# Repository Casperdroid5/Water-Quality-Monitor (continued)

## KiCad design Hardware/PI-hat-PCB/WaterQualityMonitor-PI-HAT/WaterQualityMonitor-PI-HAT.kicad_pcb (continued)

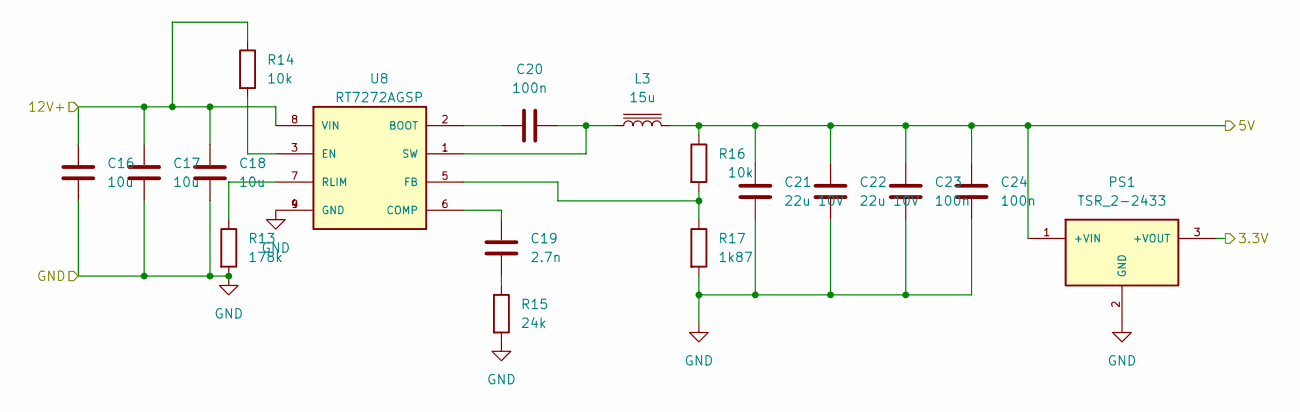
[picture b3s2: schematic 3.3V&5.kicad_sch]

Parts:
C16, C17, C18: 10u; C_1206_3216Metric_Pad1.33x1.80mm_HandSolder
C19: 2.7n; C_1206_3216Metric_Pad1.33x1.80mm_HandSolder
C20, C23, C24: 100n; C_1206_3216Metric_Pad1.33x1.80mm_HandSolder
C21, C22: 22u 10V; C_1206_3216Metric_Pad1.33x1.80mm_HandSolder
L3: 15u; L_1206_3216Metric_Pad1.22x1.90mm_HandSolder
PS1: TSR_2-2433; Converter_DCDC_TRACO_TSR-1_THT; PARTREV May 14, 2020
R13: 178k; R_1206_3216Metric_Pad1.30x1.75mm_HandSolder
R14, R16: 10k; R_1206_3216Metric_Pad1.30x1.75mm_HandSolder
R15: 24k; R_1206_3216Metric_Pad1.30x1.75mm_HandSolder
R17: 1k87; R_1206_3216Metric_Pad1.30x1.75mm_HandSolder
U8: RT7272AGSP; SOIC127P599X175-9N; PARTREV June 2015

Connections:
3.3V: PS1.3 (+VOUT); also elsewhere on the board
5V: C21.2, C22.2, C23.2, C24.1, L3.2, PS1.1 (+VIN), R16.1; also elsewhere on the board
12V+: C16.1, C17.1, C18.1, R14.1, U8.8 (VIN); also elsewhere on the board
GND: C16.2, C17.2, C18.2, C21.1, C22.1, C23.1, C24.2, PS1.2 (GND), R13.2, R15.2, R17.2, U8.4 (GND), U8.9 (GND); also elsewhere on the board
unnamed: C19.1, R15.1
unnamed: C19.2, U8.6 (COMP)
unnamed: C20.1, U8.2 (BOOT)
unnamed: C20.2, L3.1, U8.1 (SW)
unnamed: R13.1, U8.7 (RLIM)
unnamed: R14.2, U8.3 (EN)
unnamed: R16.2, R17.1, U8.5 (FB)

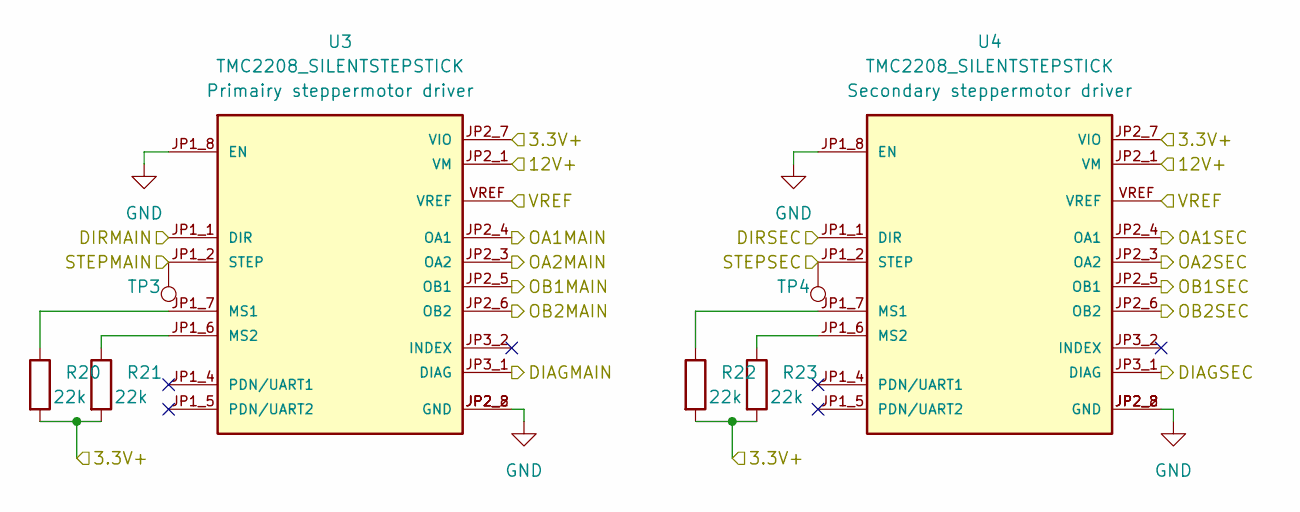
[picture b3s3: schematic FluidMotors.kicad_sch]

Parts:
R20, R21, R22, R23: 22k; R_1206_3216Metric_Pad1.30x1.75mm_HandSolder
TP3, TP4: TestPoint; TestPoint_Keystone_5019_Minature
U3, U4: TMC2208_SILENTSTEPSTICK

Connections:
3.3V: R20.2, R21.2, R22.2, R23.2, U3.JP2_7 (VIO), U3.VREF, U4.JP2_7 (VIO), U4.VREF; also elsewhere on the board
12V+: U3.JP2_1 (VM), U4.JP2_1 (VM); also elsewhere on the board
/FluidMotors/DIAGMAIN: U3.JP3_1 (DIAG)
/FluidMotors/DIAGSEC: U4.JP3_1 (DIAG)
/FluidMotors/OA1MAIN: U3.JP2_4 (OA1); also elsewhere on the board
/FluidMotors/OA1SEC: U4.JP2_4 (OA1); also elsewhere on the board
/FluidMotors/OA2MAIN: U3.JP2_3 (OA2); also elsewhere on the board
/FluidMotors/OA2SEC: U4.JP2_3 (OA2); also elsewhere on the board
/FluidMotors/OB1MAIN: U3.JP2_5 (OB1); also elsewhere on the board
/FluidMotors/OB1SEC: U4.JP2_5 (OB1); also elsewhere on the board
/FluidMotors/OB2MAIN: U3.JP2_6 (OB2); also elsewhere on the board
/FluidMotors/OB2SEC: U4.JP2_6 (OB2); also elsewhere on the board
DIRMAIN: U3.JP1_1 (DIR); also elsewhere on the board
DIRSEC: U4.JP1_1 (DIR); also elsewhere on the board
GND: U3.JP1_8 (EN), U3.JP2_2 (GND), U3.JP2_8 (GND), U4.JP1_8 (EN), U4.JP2_2 (GND), U4.JP2_8 (GND); also elsewhere on the board
unnamed: R21.1, U3.JP1_6 (MS2)
unnamed: R20.1, U3.JP1_7 (MS1)
unnamed: R23.1, U4.JP1_6 (MS2)
unnamed: R22.1, U4.JP1_7 (MS1)
STEPMAIN: TP3.1, U3.JP1_2 (STEP); also elsewhere on the board
STEPSEC: TP4.1, U4.JP1_2 (STEP); also elsewhere on the board

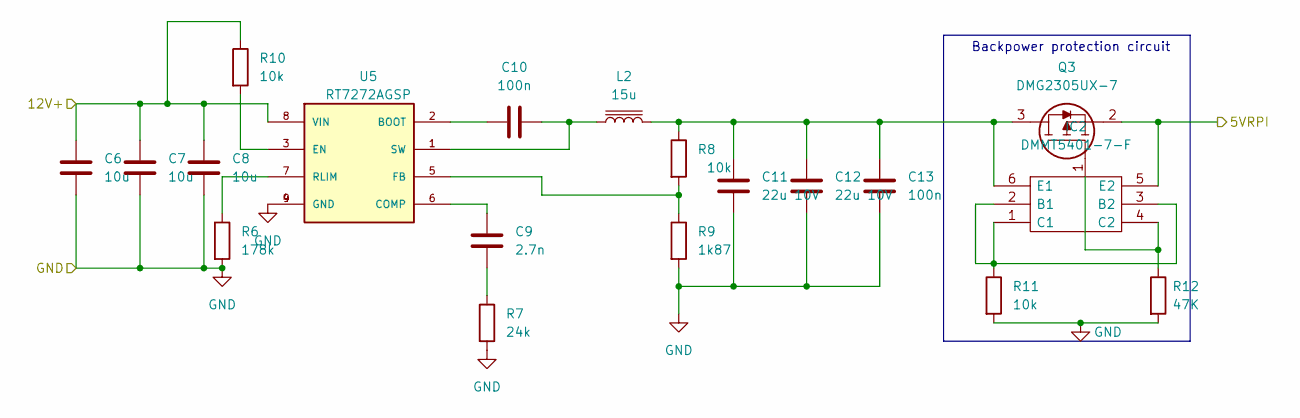
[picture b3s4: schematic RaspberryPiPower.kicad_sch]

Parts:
C6, C7, C8: 10u; C_1206_3216Metric_Pad1.33x1.80mm_HandSolder
C9: 2.7n; C_1206_3216Metric_Pad1.33x1.80mm_HandSolder
C10, C13: 100n; C_1206_3216Metric_Pad1.33x1.80mm_HandSolder
C11, C12: 22u 10V; C_1206_3216Metric_Pad1.33x1.80mm_HandSolder
IC2: DMMT5401-7-F; SOT95P285X140-6N; Mouser Part Number 621-DMMT5401-7-F
L2: 15u; L_1206_3216Metric_Pad1.22x1.90mm_HandSolder
Q3: DMG2305UX-7; SOT91P240X110-3N_DMG2305UX-7; Mouser Part Number 621-DMG2305UX-7
R6: 178k; R_1206_3216Metric_Pad1.30x1.75mm_HandSolder
R7: 24k; R_1206_3216Metric_Pad1.30x1.75mm_HandSolder
R8, R10, R11: 10k; R_1206_3216Metric_Pad1.30x1.75mm_HandSolder
R9: 1k87; R_1206_3216Metric_Pad1.30x1.75mm_HandSolder
R12: 47K; R_1206_3216Metric_Pad1.30x1.75mm_HandSolder
U5: RT7272AGSP; SOIC127P599X175-9N; PARTREV June 2015

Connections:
5VRPI: IC2.5 (E2), Q3.2; also elsewhere on the board
12V+: C6.1, C7.1, C8.1, R10.1, U5.8 (VIN); also elsewhere on the board
GND: C6.2, C7.2, C8.2, C11.1, C12.1, C13.1, R6.2, R7.2, R9.2, R11.2, R12.2, U5.4 (GND), U5.9 (GND); also elsewhere on the board
unnamed: C9.1, R7.1
unnamed: C9.2, U5.6 (COMP)
unnamed: C10.1, U5.2 (BOOT)
unnamed: C10.2, L2.1, U5.1 (SW)
unnamed: C11.2, C12.2, C13.2, IC2.6 (E1), L2.2, Q3.3, R8.1
unnamed: IC2.1 (C1), IC2.2 (B1), IC2.3 (B2), R11.1
unnamed: IC2.4 (C2), Q3.1, R12.1
unnamed: R6.1, U5.7 (RLIM)
unnamed: R8.2, R9.1, U5.5 (FB)
unnamed: R10.2, U5.3 (EN)

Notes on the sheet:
Backpower protection circuit

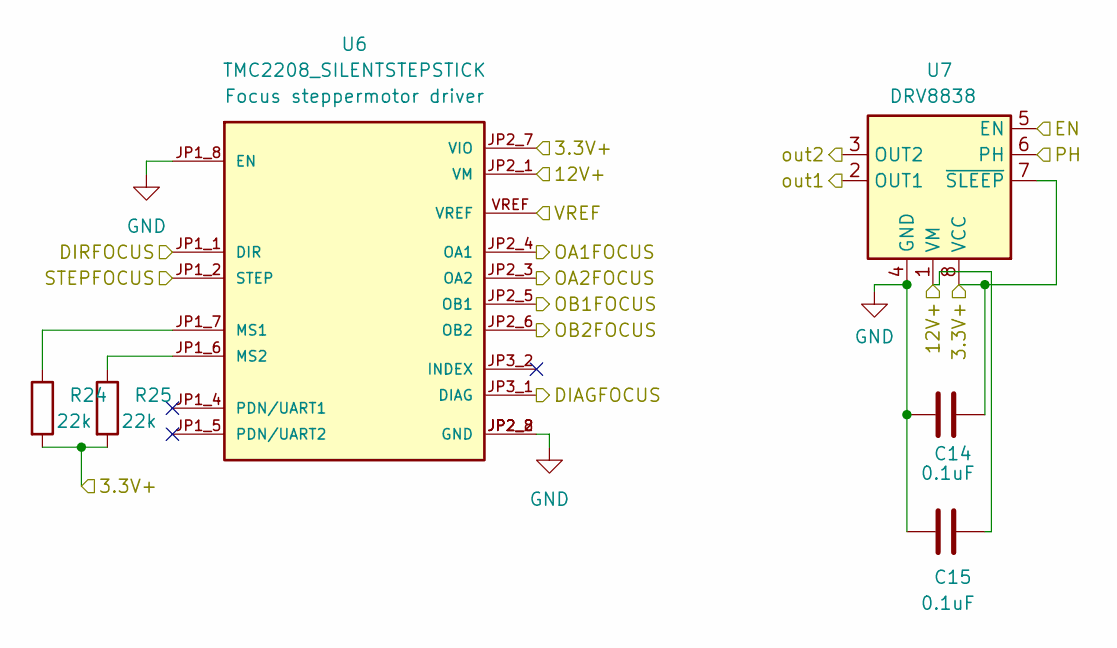
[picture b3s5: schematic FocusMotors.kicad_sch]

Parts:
C14, C15: 0.1uF; C_1206_3216Metric_Pad1.33x1.80mm_HandSolder
R24, R25: 22k; R_1206_3216Metric_Pad1.30x1.75mm_HandSolder
U6: TMC2208_SILENTSTEPSTICK
U7: DRV8838; WSON-8-1EP_2x2mm_P0.5mm_EP0.9x1.6mm

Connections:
3.3V: C14.2, R24.2, R25.2, U6.JP2_7 (VIO), U6.VREF, U7.7 (~SLEEP), U7.8 (VCC); also elsewhere on the board
12V+: C15.2, U6.JP2_1 (VM), U7.1 (VM); also elsewhere on the board
/FocusMotors/DIAGFOCUS: U6.JP3_1 (DIAG)
/FocusMotors/OA1FOCUS: U6.JP2_4 (OA1); also elsewhere on the board
/FocusMotors/OA2FOCUS: U6.JP2_3 (OA2); also elsewhere on the board
/FocusMotors/OB1FOCUS: U6.JP2_5 (OB1); also elsewhere on the board
/FocusMotors/OB2FOCUS: U6.JP2_6 (OB2); also elsewhere on the board
/FocusMotors/out1: U7.2 (OUT1); also elsewhere on the board
/FocusMotors/out2: U7.3 (OUT2); also elsewhere on the board
DIRFOCUS: U6.JP1_1 (DIR); also elsewhere on the board
ENDRV: U7.5 (EN); also elsewhere on the board
GND: C14.1, C15.1, U6.JP1_8 (EN), U6.JP2_2 (GND), U6.JP2_8 (GND), U7.4 (GND), U7.9 (GND); also elsewhere on the board
unnamed: R25.1, U6.JP1_6 (MS2)
unnamed: R24.1, U6.JP1_7 (MS1)
PHADRV: U7.6 (PH); also elsewhere on the board
STEPFOCUS: U6.JP1_2 (STEP); also elsewhere on the board

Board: 2 copper layers, 101 parts (0 on the bottom side), 91 nets, no tracks yet.

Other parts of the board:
MH1, MH2, MH3, MH4: MountingHole_2.7mm_M2.5

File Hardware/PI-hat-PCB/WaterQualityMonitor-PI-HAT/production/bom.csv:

Designator,Footprint,Quantity,Value,LCSC Part #
C1,SOIC127P600X175-8N,1,10uF,
"C10, C13, C20, C23, C24",C_1206_3216Metric_Pad1.33x1.80mm_HandSolder,5,100n,
"C11, C12, C21, C22",C_1206_3216Metric_Pad1.33x1.80mm_HandSolder,4,22u 10V,
"C14, C15, C2",C_1206_3216Metric_Pad1.33x1.80mm_HandSolder,3,0.1uF,
"C16, C17, C18, C5, C6, C7, C8",C_1206_3216Metric_Pad1.33x1.80mm_HandSolder,7,10u,
"C19, C9",C_1206_3216Metric_Pad1.33x1.80mm_HandSolder,2,2.7n,
C3,C_1206_3216Metric_Pad1.33x1.80mm_HandSolder,1,47uF,
C4,C_1206_3216Metric_Pad1.33x1.80mm_HandSolder,1,4.7uF,
D1,SESD0402X1UN0020090,1,SESD0402X1UN-0020-090,
D2,OVLEW1CB9,1,OVLEW1CB9,
D3,DIOM4336X265N,1,SMBJ26A,
F1,Fuse_1206_3216Metric_Pad1.42x1.75mm_HandSolder,1,0.5A,
F2,Fuse_1206_3216Metric_Pad1.42x1.75mm_HandSolder,1,4A,
F3,Fuse_1206_3216Metric_Pad1.42x1.75mm_HandSolder,1,3.2A,
F4,Fuse_1206_3216Metric_Pad1.42x1.75mm_HandSolder,1,10A,
FB1,L_1206_3216Metric_Pad1.22x1.90mm_HandSolder,1,150uH,
IC1,SOIC127P600X175-8N,1,"P82B96TD,118",
IC2,SOT95P285X140-6N,1,DMMT5401-7-F,
"J1, J2, J3",TerminalBlock_Altech_AK300-4_P5.00mm,3,Screw_Terminal_01x04,
"J10, J8",PinHeader_1x02_P2.54mm_Vertical,2,Conn_01x02_Male,
"J11, J9",PinHeader_1x02_P2.54mm_Vertical,2,Conn_01x05_Male,
J4,TerminalBlock_Altech_AK300-2_P5.00mm,1,Screw_Terminal_01x02,
J5,BarrelJack_Wuerth_6941xx301002,1,Jack-DC 12V+,
J6,JST_SM04B-SRSS-TB(LF)(SN),1,SM04B-SRSS-TB(LF)(SN),
J7,MODULE_RASPBERRY_PI_3_MODEL_B+,1,RASPBERRYPI-40-PIN-GPIO,
L1,L_1206_3216Metric_Pad1.22x1.90mm_HandSolder,1,4.7uH,
"L2, L3",L_1206_3216Metric_Pad1.22x1.90mm_HandSolder,2,15u,
M1,PinHeader_1x02_P2.54mm_Vertical,1,Fan,
PE1,TerminalBlock_Altech_AK300-2_P5.00mm,1,PeltierElement,
PS1,Converter_DCDC_TRACO_TSR-1_THT,1,TSR_2-2433,
"Q1, Q2",IRL540SPBF,2,IRL540SPBF,
Q3,SOT91P240X110-3N_DMG2305UX-7,1,DMG2305UX-7,
R1,R_1206_3216Metric_Pad1.30x1.75mm_HandSolder,1,0.2,
"R10, R11, R14, R16, R4, R5, R8",R_1206_3216Metric_Pad1.30x1.75mm_HandSolder,7,10k,
R12,R_1206_3216Metric_Pad1.30x1.75mm_HandSolder,1,47K,
"R13, R6",R_1206_3216Metric_Pad1.30x1.75mm_HandSolder,2,178k,
"R15, R7",R_1206_3216Metric_Pad1.30x1.75mm_HandSolder,2,24k,
"R17, R9",R_1206_3216Metric_Pad1.30x1.75mm_HandSolder,2,1k87,
R2,R_1206_3216Metric_Pad1.30x1.75mm_HandSolder,1,5.1,
R3,R_1206_3216Metric_Pad1.30x1.75mm_HandSolder,1,1.20KOHM-0603-1_10W-1%,
U1,Texas_HTSOP-8-1EP_3.9x4.9mm_P1.27mm_EP2.95x4.9mm_Mask2.4x3.1mm_ThermalVias,1,DRV8870DDA,
U2,SOT65P210X110-5N,1,TPS61169DCKR,
"U3, U4, U6",TMC2208_SILENTSTEPSTICK,3,TMC2208_SILENTSTEPSTICK,
"U5, U8",SOIC127P599X175-9N,2,RT7272AGSP,
U7,WSON-8-1EP_2x2mm_P0.5mm_EP0.9x1.6mm,1,DRV8838,

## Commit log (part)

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2022-10-10 First classes init
2022-10-10 enh pcb component layout
2022-10-10 all groups created
2022-10-10 general layout created pcb
2022-10-10 ungrouped everything
2022-10-11 enh component layout
2022-10-11 added testpoints
2022-10-11 Removed LEDS
2022-10-11 added motorclass
2022-10-11 converstation added, enh classes
2022-10-12 changed fuse ratings and added mousernrs
2022-10-12 Started changing capacitor types and sizes
2022-10-12 added new led driver and led to schematic and pcb
2022-10-12 enhanced schematic
    removed led,
    added switch
2022-10-13 added jeroen's new led driver ic
2022-10-13 cleanup
2022-10-13 fixed github and updated pcb
    Fixed github by deleting head and main in origin map
2022-10-13 changed 0.1ufs to 100nf (more common value)
2022-10-13 bom file fixed
2022-10-13 finished BOM file
2022-10-17 routing started again
2022-10-17 routing continued
2022-10-17 routing finished and started ERC
2022-10-17 ERC finished
    0 errors
    0 warnings (some exclusions made)
2022-10-17 improved silkscreen
2022-10-17 improved silkscreen
    added gpio and power silkscreen
2022-10-17 added silkscreen motor selectors 12V/24V
2022-10-17 enh gpio + pwr silkscreen
2022-10-17 improved board outline
2022-10-17 enh wiring and camera hole
2022-10-19 continue high power lines
2022-10-19 removed thick traces
2022-10-21 spacing wires
2022-10-31 Worked on presentation and wiring pcb
    ERC: 0 error, 30 warnings
2022-10-31 fixed parity problem ERC: 0 err 0 war
2022-10-31 increased width stepper trace and rerun drc 0,0
2022-10-31 improved wiring
2022-10-31 added silkscreen on back
    added useful board information
    added logo to files
2022-10-31 added conversation with johan
2022-10-31 cleanup and v0.1 archived
2022-10-31 V0.1 rounded tracks archived
2022-10-31 updated V0.1 track spacing and archived
2022-10-31 improved ppt
2022-11-01 changes made after call with Jan
2022-11-01 Unit test pwm written
2022-11-01 started adding range for pwm
2022-11-01 fixed max value bug
2022-11-01 Added extra comments to unit test pwm
2022-11-01 Wrote unit test for peltier TBT
2022-11-01 improved pwm code by using booleans
2022-11-01 fixed SetTemperature values
2022-11-01 fixed SetTemperature function...
2022-11-01 Still fixing SetTemp
2022-11-01 Still trying...
2022-11-01 Swapped frequency and dutycycle (cause of error)
2022-11-01 finished unit test for peltier
2022-11-01 improved unit test peltier readability and delays
2022-11-01 Started on powergpio unit test
2022-11-01 tried making child class from POWERGPIO class
2022-11-01 Presumably created a unit test for powergpio
2022-11-01 Started on MOTORS class variables
2022-11-01 added usefull states for debugging
2022-11-02 return self state tryout excersise
2022-11-02 tryout getstate2
2022-11-02 tryout4
2022-11-02 tryout5
2022-11-02 added enum class and tried out on pwm class
2022-11-02 changed state.ON to state.ON.name
2022-11-02 Created fan.py and constants.py class. added all constants to classes
2022-11-02 added pdf's to schematic v0.1
2022-11-02 Worked on stepper motor unit test
2022-11-02 improved motor unit test.
2022-11-02 fixed naming error
2022-11-02 Added raspberry pi GPIO pins to constants
2022-11-02 created microscoppeled class and removed unit test from pwm class
2022-11-02 motor class refined, working on pin config
2022-11-02 renamed stepper motor1 to class
2022-11-02 fixing unit tests motors (changing numbers and names)
2022-11-02 repaired fan class, now with regular pwm
2022-11-02 restored fan again with better class name
2022-11-02 Finished rewriting peltier pwm
2022-11-02 rewriting voicecoil to pwm "normal"
2022-11-02 cleaned up classes and rewritten powergpio (PWM)
2022-11-02 renamed and moved files
2022-11-02 Now really fixed.
2022-11-02 trying to fix stepper motor errors (no permission to update gpio)
2022-11-03 Wrote unit test for steppermotors
2022-11-03 figured out that pigpio uses BCM numbering, not GPIO pin numbering. Making changes
2022-11-03 changed all "pin" to GPIOPin and finished voicecoild unit test
2022-11-03 setmotorstep removed step +1
2022-11-04 Tried to get pyqt working, and made template for testreport
2022-11-08 removed pwm from enable (bool works)
2022-11-08 init.py added pigpio now inplemented as program, not at boot anymore
2022-11-08 changed some values to make more sense
2022-11-08 improved values in stepper motor
2022-11-09 improved functions usage in voicecoilmotors pwm to write
2022-11-09 improved voicecoil readability and some functions
2022-11-10 i2c esd circuit, log, picam2 main
2022-11-14 add esd, log, extra order
2022-11-14 added usefull notes
2022-11-14 added button.py
2022-11-14 trying camera
2022-11-14 pyqt5 code examples added
2022-11-14 deleted button.py
2022-11-14 working on docking for multiple widgets in main windows
2022-11-14 added example code from github
2022-11-16 changed some values for testing with v0.1 pcb
2022-11-16 stepper motor tests
2022-11-17 changed of on for drv8838
2022-11-17 added raspberry pi i2c adt7410 test
2022-11-17 removed py i2c test
2022-11-17 uploaded i2c test again.
2022-11-17 log added.
2022-11-21 Started on V0.2 PCB and V1.3 schematic
    -added new power circuit for RPI (removed old one rt7272)
    -made daughter schematics sheets smaller
2022-11-21 started on V0.2 schematic fixes
    -fixed vcc on drv8838
    -added bypass to backpower protection circuit rpi
    -removed unnecessary capacitors
    -removed esd ic's
    -added esd tvs diodes
    -made schematic more readable
2022-11-21 removed protection diodes on PGPIO
2022-11-21 removed all wiring
2022-11-21 removed some fuses
2022-11-21 added silkscreens
2022-11-21 added logo
2022-11-22 finished wiring, running ERC
2022-11-22 ERC errors resolved
2022-11-22 Added silkscreen to buttom header (and figured out that header was wrong, again)
2022-11-22 started over with pcb. Fresh start
2022-11-22 removed edge cut error.
2022-11-22 finished component placement
2022-11-22 Finished silkscreens for now
    -front
    -back
2022-11-22 fixed github
2022-11-22 High power lines routed
    -i think i got them all at least. width 0.600mm
2022-11-22 5.0V and 3.3V lines finished
    -If I did not miss anything
2022-11-22 ERC cleared
    - 0 errors
    - 0 warnings
2022-11-22 improved traces
2022-11-22 added interactive BOM
2022-11-22 added jlc fabrication toolkit
2022-11-24 improved 4th order list
2022-11-24 finished order lists
2022-11-24 started on v0.3 pcb
2022-11-28 improved LCSC + schematic values and order lists
2022-11-28 removed old examples
2022-11-28 removed more examples
2022-11-28 working on general gui layout
2022-11-28 Created extra group
2022-11-28 Worked on motor gui element
2022-11-28 improved group 2 and 4 layout
2022-11-29 added PowerGPIO box and attributes
2022-11-29 removed sliders
2022-11-29 added extra motor atributes
2022-11-29 Improved motor layout
2022-11-29 removed disable function from panic buttons
2022-11-29 updated log
2022-11-30 added doc files
    -stepper motor water resolution test report
    -tmc2209 datasheets and notes
    -pcb v0.3 improvements
2022-11-30 added excel sheet
2022-12-05 Wrote documentation and finally got the multiple stepper drivers working on uart
2022-12-07 changed main and motor schematics
    MAIN:
    -removed some caps
    -changed cap values to 50v (for consistency)
    -removed FB1
    MOTORS:
    -Started replacing the 2208 with the TMC2209
2022-12-07 exchanged tmc2208 for tmc2209 in focusmotor sheet
2022-12-07 changed 0B1 0A1 etc to M1B and M2A etc
2022-12-07 added uart resistors and info
2022-12-07 changed footprints (TMC2208->2209) and names
2022-12-07 removed resistors for uart (it was a test)
2022-12-07 added new logo V0.2
2022-12-07 tidy up schematic
2022-12-07 added gpio breakouts gpio23&24
2022-12-07 added uart adress jumpers
2022-12-07 repositioned capacitor
2022-12-07 changed GPIO numbers to external header
2022-12-07 improved pcb layout
2022-12-07 fixed the annotation bug
2022-12-08 changed some component values in RPI power circuit
    New components
    -lm2596s -5.0
    -ss510
    Removed:
    feedback resistors
2022-12-08 improved RPI Power circuit
    -added capacitors and values
2022-12-08 added tmc2208 footprints to 2209 schematic symbol
    interchangable since the TMC drivers have roughly the same pinout.
2022-12-08 improved peltier schematic layout
2022-12-08 improved overal schematic layout
2022-12-08 Removed Enable control from stepper drivers and started V0.3 pcb redesign
2022-12-08 tht component layout concept 1. COMPACT DESIGN
2022-12-08 back layout improvement
2022-12-08 board outline size reduced significantly
2022-12-08 back component grouping completed
2022-12-08 added logo and other silkscreen components
2022-12-08 more silkscreen improvements
2022-12-08 swapped cooling fan en PGIO position
2022-12-08 re positioned some components
2022-12-09 Removed all traces. Trying autorouter
    freerouting
2022-12-12 Removed GND connection from phoenix headers
2022-12-12 wiring complete
    ERC
    errors: 0
    warnings: 17
2022-12-12 Resolved some ERC warnings
    only warnings left are on stepper motor drivers, i can ignore those.
2022-12-12 reverted manually and added rounded traces design V0.3
2022-12-12 Started 4 layer board
    wired high power lanes for steppers and other outputs
2022-12-12 4 layer PCB finished
    ERC
    Error: 0
    Warnings: 18
2022-12-12 Warnings reduced to 10.
2022-12-13 worked on PCB and schematic designs
    many small changes and some big schematic changes (motors)
2022-12-13 tmc2209 pinout changed (moved RX)
2022-12-13 added back B-EMF diodes to PGIO's
2022-12-13 impro schem readability
2022-12-14 Rewired RX pins on pcb
2022-12-14 improved some traces
2022-12-14 Improved grounding for rpi power circuit components
2022-12-14 added purposes to sch. + improved silkscreen
2022-12-15 added production files and bom
2022-12-15 repo cleanup and added ChatGPT to kicad doc
2022-12-15 improved conversation map
2022-12-15 big cleanup
2022-12-15 continued writing on stepper motor
2022-12-16 changed up the f fab outline from some components
2022-12-19 worked on documentation and changed some code for testing the peltier
2022-12-19 improved BOM file for schematic and added improvements V0.4 for rastaban pcb
2022-12-19 wrote more text for main report
    -PMS
    -pwr gpio
    -peltier
    -etc
2022-12-20 added focus motor script to test
2022-12-20 renamed testfile
2022-12-20 renamed files
2022-12-20 added plugin to kicad6
2022-12-20 wrote a lot of extra text in my report
2022-12-21 added doxygen.
2022-12-21 removed latex
2022-12-22 new system architecture scheme made
2022-12-22 chat gpt added in report. exported library for v0.3
2023-01-09 changed 'x' to PeltierA
2023-01-09 Finished UARTsteppermotor control software (not tested)
2023-01-09 added values to instance
2023-01-09 minor value changes (code not tested)
2023-01-09 Cleanup uart stepper driver code
2023-01-09 Wrote piece on PCB versions.
2023-01-09 cleanup and added note for uart tests
2023-01-09 new doxygen generated
2023-01-10 created new order
2023-01-11 updated tmc2209 map
2023-01-16 Documentation improvements
2023-01-16 General improvements to main report
2023-01-17 improved docs and removed docs that are no longer required.
    And a random picture...
2023-01-17 cleanup documentation map
2023-01-17 added captions to pictures
2023-01-17 update on uart final fix in documentation!
2023-01-18 updated gitignore
2023-01-18 changed src file location and cleanup
2023-01-18 same as previous commit
2023-01-18 testscript made
2023-01-18 changed variable name
2023-01-18 added pigpio
2023-01-18 added stepper motor class
2023-01-18 added superinit()
2023-01-18 improved minor code formating
2023-01-18 code readability updated
2023-01-18 datasheet added
2023-01-19 Fixed the stepper motor issues with UART
    -documentation on fix added
    -updated scripts to work with uart
    -added uart logic analyser data for documentation
2023-01-19 changed some parameters on vactual test
2023-01-19 updated uart stepper motor script
2023-01-19 fixed bug uartstep
2023-01-19 parameter updates
2023-01-19 value uart adress cha
2023-01-19 added * and changed parameters
2023-01-19 UARTsteppermotor is now functional
2023-01-19 extended test, rotating forward and backwards
2023-01-23 Finished V0.2 of main report
2023-01-24 updated main report to v0.3
2023-01-25 formatted code
